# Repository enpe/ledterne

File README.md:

# LEDterne

## Required Equipment

- Suggested hardware lists:
	1. [mikrocontroller.net][0]
- Atmel AVRISP MKII ([Amazon][1])
- Evaluation board ([ehajo][2], [Pollin][3], [Amazon][4])
- Adapter cable, 10P-to-6P ([mikocontroller.net][7], [Amazon 1][5], [Amazon 2][6])
- Power supply (~9V)
- Bread board ([Amazon][8])
- ATMEGA8-16PU ([Amazon][9])
- Steckbrücken 
- Multimeter
- Resistors
- LEDs (e.g. RGB)
- Software (compiler, etc.) ([mikrocontroller.net][20])

## TODO

- Experiment with LEDs
	- Adjust series resistors for balanced LED brightness of the different colors
	- Try diffusing light from the LEDs
- Add some interesting animations
- Add a push button for switching between a number of animations, constant colors etc.
	- Can use pin PD3's external interrupt capabilities instead of polling one of the other free pins
- Make it battery-driven
- Maybe make the PWM smarter for improved energy saving
	- Alternative 1:
		- Avoid generating interrupts for every single possible step in a PWM cycle
		- Compute only the required timeout periods for all 3×5 outputs instead
	- Alternative 2 (easier than 1):
		- Avoid generating interrupts for every single possible step in a PWM cycle
		- Compute only the required timeout periods for all (currently 32) different duty cycles that we actually use
		- This is not as efficient as alternative 1, but it is much simpler to implement since it is not data-dependent (does not change with the desired LED brightness (i.e. with the animations))
- Maybe improve PWM resolution for smoother fading
- Maybe implement the animations using coroutines/generators instead of letting the animation do the diplay update
	- https://en.wikipedia.org/wiki/Generator_%28computer_science%29
	- http://www.chiark.greenend.org.uk/~sgtatham/coroutines.html

### Battery holder and rod
- Dimensions of [mignon/AA batteries][21]:
	- Diameter:  13.5-14.5 mm
    - Length:    49.2-50.5 mm
- General idea:
    1. Rod of the lantern
    	- Thin aluminum tube (outer diameter <= 10mm).
    	- Drill a small hole near the top end of the rod (wire outlet + hook for
    	  lantern).
    	- Close the top end with a small cap (or leave it open).
    	- Take 2-3 corks and drill holes into the centers to fit the rod.
    	- Cut outside part of the corks to fit (tightly) into the tube of 
    	  battery holder.
    	- Slide the corks over the lower end of the rod.
    	- Insert 2 wires from lower end of the rod to the outlet at the top end.
    2. Battery holder
		- Tube with inner diameter of ~15-16 mm.
		- In the first third of the tube, drill a hole for a small switch.
		- Add 2 wires: one from switch to the lower end of the tube the other
		  from one end of the tube to the other.
		- Connect the switch with one wire of the rod, and connect the remaining
		  two wires
		- Connect upper end of the battery holder with the rod.
		- Fill with 3xAA batteries.
		- Add a spring at the lower end and connect it to the wire.
		- Close lower end with a plastic cap (Lamellenstopfen)
- Other DIY project for battery holders (in no particular order):
	- http://makezine.com/2009/08/14/how-to-free-diy-battery-holders/
	- http://makezine.com/2015/08/02/make-a-stylish-flashlight-out-of-kitchen-trash/
	- http://www.instructables.com/id/Bicycle-Battery-Holder-3-x-AA/
	- http://www.instructables.com/id/Easy-custom-battery-holders/
	- http://www.instructables.com/id/Easy-DIY-Battery-Holder/
	- http://www.instructables.com/id/PVC-tube-battery-AA-battery-holder/
	- http://www.pcbheaven.com/projectpages/DIY_Battery_Pack/

[0]: http://www.mikrocontroller.net/articles/AVR-Tutorial:_Equipment
[1]: http://www.amazon.de/Atmel-Programmer-ATMEL-AVR-ISP-MKII/dp/B00CASCN2S
[2]: http://www.ehajo.de/ateval-atmel-evaluationboard.html 
[3]: http://www.pollin.de/shop/dt/NTI5OTgxOTk-/Bausaetze_Module/Entwicklerboards/ATMEL_Evaluations_Board_V2_0_1_Fertigmodul.html
[4]: http://www.amazon.de/Atmel-Fertiggerät-Atmel-Evaluations-Board-V2-0/dp/B004BMJZ0O
[5]: http://www.amazon.de/Convert-Standard-Adapter-STK500-AVRISP/dp/B00P783JIU
[6]: http://www.amazon.de/Adapter-Kit-10polig-Atmel-Programmer/dp/B004D2TFYI
[7]: http://www.mikrocontroller.net/articles/AVR_In_System_Programmer#ISP
[8]: http://www.amazon.de/Steckbrett-Breadboard-Experimentierboard-Steckplatine-Kontakte/dp/B009P04XWW
[9]: http://www.amazon.de/ATMEGA8-16PU-Atmel-Microcontroller-MEGA-DIP-28/dp/9827046934
[20]: http://www.mikrocontroller.net/articles/AVR_und_Linux
[21]: https://de.wikipedia.org/wiki/Mignon_%28Batterie%29

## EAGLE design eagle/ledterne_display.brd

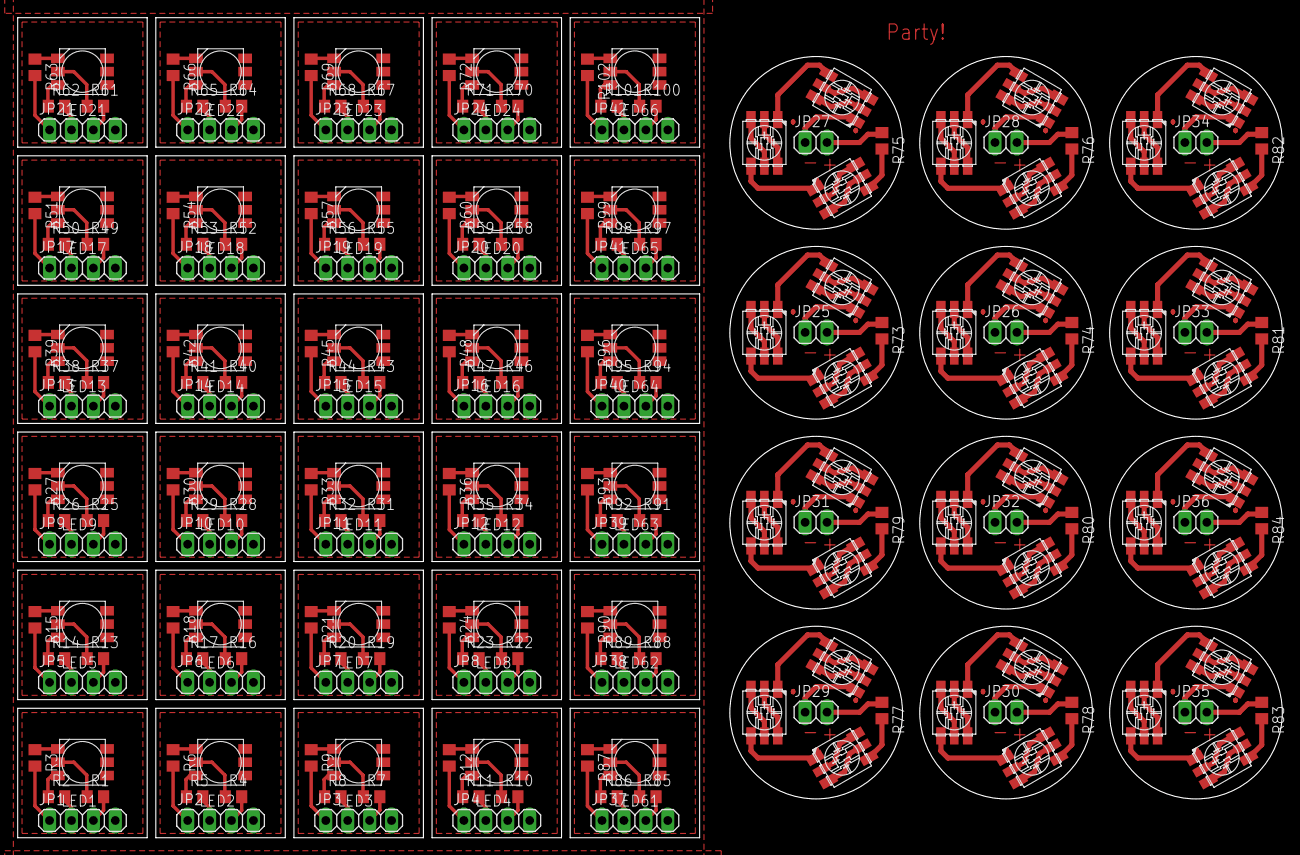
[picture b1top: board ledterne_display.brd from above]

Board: 2 copper layers, 146.5 x 95.0 mm, 210 parts (0 on the bottom side), 342 nets.

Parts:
JP1, JP2, JP3, JP4, JP5, JP6, JP7, JP8, JP9, JP10, JP11, JP12, JP13, JP14, JP15, JP16, JP17, JP18, JP19, JP20, JP21, JP22, JP23, JP24, JP37, JP38, JP39, JP40, JP41, JP42: 1X04
JP25, JP26, JP27, JP28, JP29, JP30, JP31, JP32, JP33, JP34, JP35, JP36: 1X02
LED1, LED2, LED3, LED4, LED5, LED6, LED7, LED8, LED9, LED10, LED11, LED12, LED13, LED14, LED15, LED16, LED17, LED18, LED19, LED20, LED21, LED22, LED23, LED24, LED61, LED62, LED63, LED64, LED65, LED66: RGB-5252; SMD_5252
LED25, LED26, LED27, LED28, LED29, LED30, LED31, LED32, LED33, LED34, LED35, LED36, LED37, LED38, LED39, LED40, LED41, LED42, LED43, LED44, LED45, LED46, LED47, LED48, LED49, LED50, LED51, LED52, LED53, LED54, LED55, LED56, LED57, LED58, LED59, LED60: LUCKYLIGHT-R5050; PLCC-6
R1, R2, R3, R4, R5, R6, R7, R8, R9, R10, R11, R12, R13, R14, R15, R16, R17, R18, R19, R20, R21, R22, R23, R24, R25, R26, R27, R28, R29, R30, R31, R32, R33, R34, R35, R36, R37, R38, R39, R40, R41, R42, R43, R44, R45, R46, R47, R48, R49, R50, R51, R52, R53, R54, R55, R56, R57, R58, R59, R60, R61, R62, R63, R64, R65, R66, R67, R68, R69, R70, R71, R72, R85, R86, R87, R88, R89, R90, R91, R92, R93, R94, R95, R96, R97, R98, R99, R100, R101, R102: R0805
R73, R74, R75, R76, R77, R78, R79, R80, R81, R82, R83, R84: 225; R0805

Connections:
22,5V: JP25.2, R73.1
22,5V1: JP26.2, R74.1
22,5V2: JP27.2, R75.1
22,5V3: JP28.2, R76.1
22,5V4: JP29.2, R77.1
22,5V5: JP30.2, R78.1
22,5V6: JP31.2, R79.1
22,5V7: JP32.2, R80.1
22,5V8: JP33.2, R81.1
22,5V9: JP34.2, R82.1
22,5V10: JP35.2, R83.1
22,5V11: JP36.2, R84.1
GND: JP1.4, LED1.P4, LED1.P5, LED1.P6
GND1: JP2.4, LED2.P4, LED2.P5, LED2.P6
GND2: JP3.4, LED3.P4, LED3.P5, LED3.P6
GND3: JP4.4, LED4.P4, LED4.P5, LED4.P6
GND4: JP5.4, LED5.P4, LED5.P5, LED5.P6
GND5: JP6.4, LED6.P4, LED6.P5, LED6.P6
GND6: JP7.4, LED7.P4, LED7.P5, LED7.P6
GND7: JP8.4, LED8.P4, LED8.P5, LED8.P6
GND8: JP9.4, LED9.P4, LED9.P5, LED9.P6
GND9: JP10.4, LED10.P4, LED10.P5, LED10.P6
GND10: JP11.4, LED11.P4, LED11.P5, LED11.P6
GND11: JP12.4, LED12.P4, LED12.P5, LED12.P6
GND12: JP13.4, LED13.P4, LED13.P5, LED13.P6
GND13: JP14.4, LED14.P4, LED14.P5, LED14.P6
GND14: JP15.4, LED15.P4, LED15.P5, LED15.P6
GND15: JP16.4, LED16.P4, LED16.P5, LED16.P6
GND16: JP17.4, LED17.P4, LED17.P5, LED17.P6
GND17: JP18.4, LED18.P4, LED18.P5, LED18.P6
GND18: JP19.4, LED19.P4, LED19.P5, LED19.P6
GND19: JP20.4, LED20.P4, LED20.P5, LED20.P6
GND20: JP21.4, LED21.P4, LED21.P5, LED21.P6
GND21: JP22.4, LED22.P4, LED22.P5, LED22.P6
GND22: JP23.4, LED23.P4, LED23.P5, LED23.P6
GND23: JP24.4, LED24.P4, LED24.P5, LED24.P6
GND24: JP25.1, LED27.P$1
GND25: JP26.1, LED30.P$1
GND26: JP27.1, LED33.P$1
GND27: JP28.1, LED36.P$1
GND28: JP29.1, LED39.P$1
GND29: JP30.1, LED42.P$1
GND30: JP31.1, LED45.P$1
GND31: JP32.1, LED48.P$1
GND32: JP33.1, LED51.P$1
GND33: JP34.1, LED54.P$1
GND34: JP35.1, LED57.P$1
GND35: JP36.1, LED60.P$1
GND36: JP37.4, LED61.P4, LED61.P5, LED61.P6
GND37: JP38.4, LED62.P4, LED62.P5, LED62.P6
GND38: JP39.4, LED63.P4, LED63.P5, LED63.P6
GND39: JP40.4, LED64.P4, LED64.P5, LED64.P6
GND40: JP41.4, LED65.P4, LED65.P5, LED65.P6
GND41: JP42.4, LED66.P4, LED66.P5, LED66.P6
LED_B: JP1.1, R3.2
LED_B1: JP2.1, R6.2
LED_B2: JP3.1, R9.2
LED_B3: JP4.1, R12.2
LED_B4: JP5.1, R15.2
LED_B5: JP6.1, R18.2
LED_B6: JP7.1, R21.2
LED_B7: JP8.1, R24.2
LED_B8: JP9.1, R27.2
LED_B9: JP10.1, R30.2
LED_B10: JP11.1, R33.2
LED_B11: JP12.1, R36.2
LED_B12: JP13.1, R39.2
LED_B13: JP14.1, R42.2
LED_B14: JP15.1, R45.2
LED_B15: JP16.1, R48.2
LED_B16: JP17.1, R51.2
LED_B17: JP18.1, R54.2
LED_B18: JP19.1, R57.2
LED_B19: JP20.1, R60.2
LED_B20: JP21.1, R63.2
LED_B21: JP22.1, R66.2
LED_B22: JP23.1, R69.2
LED_B23: JP24.1, R72.2
LED_B24: JP37.1, R87.2
LED_B25: JP38.1, R90.2
LED_B26: JP39.1, R93.2
LED_B27: JP40.1, R96.2
LED_B28: JP41.1, R99.2
LED_B29: JP42.1, R102.2
LED_G: JP1.2, R2.2
LED_G1: JP2.2, R5.2
LED_G2: JP3.2, R8.2
LED_G3: JP4.2, R11.2
LED_G4: JP5.2, R14.2
LED_G5: JP6.2, R17.2
LED_G6: JP7.2, R20.2
LED_G7: JP8.2, R23.2
LED_G8: JP9.2, R26.2
LED_G9: JP10.2, R29.2
LED_G10: JP11.2, R32.2
LED_G11: JP12.2, R35.2
LED_G12: JP13.2, R38.2
LED_G13: JP14.2, R41.2
LED_G14: JP15.2, R44.2
LED_G15: JP16.2, R47.2
LED_G16: JP17.2, R50.2
LED_G17: JP18.2, R53.2
LED_G18: JP19.2, R56.2
LED_G19: JP20.2, R59.2
LED_G20: JP21.2, R62.2
LED_G21: JP22.2, R65.2
LED_G22: JP23.2, R68.2
LED_G23: JP24.2, R71.2
LED_G24: JP37.2, R86.2
LED_G25: JP38.2, R89.2
LED_G26: JP39.2, R92.2
LED_G27: JP40.2, R95.2
LED_G28: JP41.2, R98.2
LED_G29: JP42.2, R101.2
LED_R: JP1.3, R1.2
LED_R1: JP2.3, R4.2
LED_R2: JP3.3, R7.2
LED_R3: JP4.3, R10.2
LED_R4: JP5.3, R13.2
LED_R5: JP6.3, R16.2
LED_R6: JP7.3, R19.2
LED_R7: JP8.3, R22.2
LED_R8: JP9.3, R25.2
LED_R9: JP10.3, R28.2
LED_R10: JP11.3, R31.2
LED_R11: JP12.3, R34.2
LED_R12: JP13.3, R37.2
LED_R13: JP14.3, R40.2
LED_R14: JP15.3, R43.2
LED_R15: JP16.3, R46.2
LED_R16: JP17.3, R49.2
LED_R17: JP18.3, R52.2
LED_R18: JP19.3, R55.2
LED_R19: JP20.3, R58.2
LED_R20: JP21.3, R61.2
LED_R21: JP22.3, R64.2
LED_R22: JP23.3, R67.2
LED_R23: JP24.3, R70.2
LED_R24: JP37.3, R85.2
LED_R25: JP38.3, R88.2
LED_R26: JP39.3, R91.2
LED_R27: JP40.3, R94.2
LED_R28: JP41.3, R97.2
LED_R29: JP42.3, R100.2
unnamed: LED1.P2, R1.1
unnamed: LED1.P3, R2.1
unnamed: LED1.P1, R3.1
unnamed: LED2.P2, R4.1
unnamed: LED2.P3, R5.1
unnamed: LED2.P1, R6.1
unnamed: LED3.P2, R7.1
unnamed: LED3.P3, R8.1
unnamed: LED3.P1, R9.1
unnamed: LED4.P2, R10.1
unnamed: LED4.P3, R11.1
unnamed: LED4.P1, R12.1
unnamed: LED5.P2, R13.1
unnamed: LED5.P3, R14.1
unnamed: LED5.P1, R15.1
unnamed: LED6.P2, R16.1
unnamed: LED6.P3, R17.1
unnamed: LED6.P1, R18.1
unnamed: LED7.P2, R19.1
unnamed: LED7.P3, R20.1
unnamed: LED7.P1, R21.1
unnamed: LED8.P2, R22.1
unnamed: LED8.P3, R23.1
unnamed: LED8.P1, R24.1
unnamed: LED9.P2, R25.1
unnamed: LED9.P3, R26.1
unnamed: LED9.P1, R27.1
unnamed: LED10.P2, R28.1
unnamed: LED10.P3, R29.1
unnamed: LED10.P1, R30.1
unnamed: LED11.P2, R31.1
unnamed: LED11.P3, R32.1
unnamed: LED11.P1, R33.1
unnamed: LED12.P2, R34.1
unnamed: LED12.P3, R35.1
unnamed: LED12.P1, R36.1
unnamed: LED13.P2, R37.1
unnamed: LED13.P3, R38.1
unnamed: LED13.P1, R39.1
unnamed: LED14.P2, R40.1
unnamed: LED14.P3, R41.1
unnamed: LED14.P1, R42.1
unnamed: LED15.P2, R43.1
unnamed: LED15.P3, R44.1
unnamed: LED15.P1, R45.1
unnamed: LED16.P2, R46.1
unnamed: LED16.P3, R47.1
unnamed: LED16.P1, R48.1
unnamed: LED17.P2, R49.1
unnamed: LED17.P3, R50.1
unnamed: LED17.P1, R51.1
unnamed: LED18.P2, R52.1
unnamed: LED18.P3, R53.1
unnamed: LED18.P1, R54.1
unnamed: LED19.P2, R55.1
unnamed: LED19.P3, R56.1
unnamed: LED19.P1, R57.1
unnamed: LED20.P2, R58.1
unnamed: LED20.P3, R59.1
unnamed: LED20.P1, R60.1
unnamed: LED21.P2, R61.1
unnamed: LED21.P3, R62.1
unnamed: LED21.P1, R63.1
unnamed: LED22.P2, R64.1
unnamed: LED22.P3, R65.1
unnamed: LED22.P1, R66.1
unnamed: LED23.P2, R67.1
unnamed: LED23.P3, R68.1
unnamed: LED23.P1, R69.1
unnamed: LED24.P2, R70.1
unnamed: LED24.P3, R71.1
unnamed: LED24.P1, R72.1
unnamed: LED27.P$2, LED27.P$6
unnamed: LED27.P$3, LED27.P$5
unnamed: LED26.P$1, LED27.P$4
unnamed: LED26.P$2, LED26.P$6
unnamed: LED26.P$3, LED26.P$5
unnamed: LED25.P$1, LED26.P$4
unnamed: LED25.P$2, LED25.P$6
unnamed: LED25.P$3, LED25.P$5
unnamed: LED25.P$4, R73.2
unnamed: LED30.P$2, LED30.P$6
unnamed: LED30.P$3, LED30.P$5
unnamed: LED29.P$1, LED30.P$4
unnamed: LED29.P$2, LED29.P$6
unnamed: LED29.P$3, LED29.P$5
unnamed: LED28.P$1, LED29.P$4
unnamed: LED28.P$2, LED28.P$6
unnamed: LED28.P$3, LED28.P$5
unnamed: LED28.P$4, R74.2
unnamed: LED33.P$2, LED33.P$6
unnamed: LED33.P$3, LED33.P$5
unnamed: LED32.P$1, LED33.P$4
unnamed: LED32.P$2, LED32.P$6
unnamed: LED32.P$3, LED32.P$5
unnamed: LED31.P$1, LED32.P$4
unnamed: LED31.P$2, LED31.P$6
unnamed: LED31.P$3, LED31.P$5
unnamed: LED31.P$4, R75.2
unnamed: LED36.P$2, LED36.P$6
unnamed: LED36.P$3, LED36.P$5
unnamed: LED35.P$1, LED36.P$4
unnamed: LED35.P$2, LED35.P$6
unnamed: LED35.P$3, LED35.P$5
unnamed: LED34.P$1, LED35.P$4
unnamed: LED34.P$2, LED34.P$6
unnamed: LED34.P$3, LED34.P$5
unnamed: LED34.P$4, R76.2
unnamed: LED39.P$2, LED39.P$6
unnamed: LED39.P$3, LED39.P$5
unnamed: LED38.P$1, LED39.P$4
unnamed: LED38.P$2, LED38.P$6
unnamed: LED38.P$3, LED38.P$5
unnamed: LED37.P$1, LED38.P$4
unnamed: LED37.P$2, LED37.P$6
unnamed: LED37.P$3, LED37.P$5
unnamed: LED37.P$4, R77.2
unnamed: LED42.P$2, LED42.P$6
unnamed: LED42.P$3, LED42.P$5
unnamed: LED41.P$1, LED42.P$4
unnamed: LED41.P$2, LED41.P$6
unnamed: LED41.P$3, LED41.P$5
unnamed: LED40.P$1, LED41.P$4
unnamed: LED40.P$2, LED40.P$6
unnamed: LED40.P$3, LED40.P$5
unnamed: LED40.P$4, R78.2
unnamed: LED45.P$2, LED45.P$6
unnamed: LED45.P$3, LED45.P$5
unnamed: LED44.P$1, LED45.P$4
unnamed: LED44.P$2, LED44.P$6
unnamed: LED44.P$3, LED44.P$5
unnamed: LED43.P$1, LED44.P$4
unnamed: LED43.P$2, LED43.P$6
unnamed: LED43.P$3, LED43.P$5
unnamed: LED43.P$4, R79.2
unnamed: LED48.P$2, LED48.P$6
unnamed: LED48.P$3, LED48.P$5
unnamed: LED47.P$1, LED48.P$4
unnamed: LED47.P$2, LED47.P$6
unnamed: LED47.P$3, LED47.P$5
unnamed: LED46.P$1, LED47.P$4
unnamed: LED46.P$2, LED46.P$6
unnamed: LED46.P$3, LED46.P$5
unnamed: LED46.P$4, R80.2
unnamed: LED51.P$2, LED51.P$6
unnamed: LED51.P$3, LED51.P$5
unnamed: LED50.P$1, LED51.P$4
unnamed: LED50.P$2, LED50.P$6
unnamed: LED50.P$3, LED50.P$5
unnamed: LED49.P$1, LED50.P$4
unnamed: LED49.P$2, LED49.P$6
unnamed: LED49.P$3, LED49.P$5
unnamed: LED49.P$4, R81.2
unnamed: LED54.P$2, LED54.P$6
unnamed: LED54.P$3, LED54.P$5
unnamed: LED53.P$1, LED54.P$4
unnamed: LED53.P$2, LED53.P$6
unnamed: LED53.P$3, LED53.P$5
unnamed: LED52.P$1, LED53.P$4
unnamed: LED52.P$2, LED52.P$6
unnamed: LED52.P$3, LED52.P$5
unnamed: LED52.P$4, R82.2
unnamed: LED57.P$2, LED57.P$6
unnamed: LED57.P$3, LED57.P$5
unnamed: LED56.P$1, LED57.P$4
unnamed: LED56.P$2, LED56.P$6
unnamed: LED56.P$3, LED56.P$5
unnamed: LED55.P$1, LED56.P$4
unnamed: LED55.P$2, LED55.P$6
unnamed: LED55.P$3, LED55.P$5
unnamed: LED55.P$4, R83.2
unnamed: LED60.P$2, LED60.P$6
unnamed: LED60.P$3, LED60.P$5
unnamed: LED59.P$1, LED60.P$4
unnamed: LED59.P$2, LED59.P$6
unnamed: LED59.P$3, LED59.P$5
unnamed: LED58.P$1, LED59.P$4
unnamed: LED58.P$2, LED58.P$6
unnamed: LED58.P$3, LED58.P$5
unnamed: LED58.P$4, R84.2
unnamed: LED61.P2, R85.1
unnamed: LED61.P3, R86.1
unnamed: LED61.P1, R87.1
unnamed: LED62.P2, R88.1
unnamed: LED62.P3, R89.1
unnamed: LED62.P1, R90.1
unnamed: LED63.P2, R91.1
unnamed: LED63.P3, R92.1
unnamed: LED63.P1, R93.1
unnamed: LED64.P2, R94.1
unnamed: LED64.P3, R95.1
unnamed: LED64.P1, R96.1
unnamed: LED65.P2, R97.1
unnamed: LED65.P3, R98.1
unnamed: LED65.P1, R99.1
unnamed: LED66.P2, R100.1
unnamed: LED66.P3, R101.1
unnamed: LED66.P1, R102.1

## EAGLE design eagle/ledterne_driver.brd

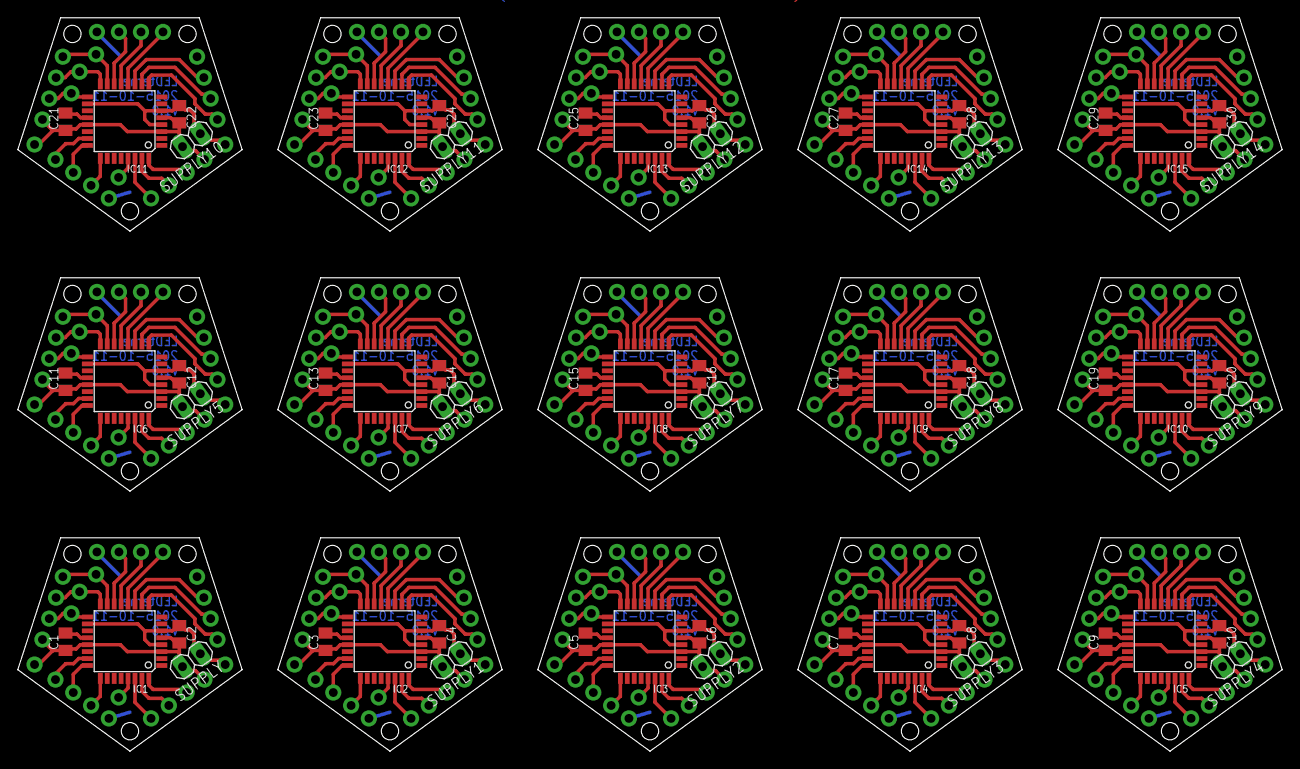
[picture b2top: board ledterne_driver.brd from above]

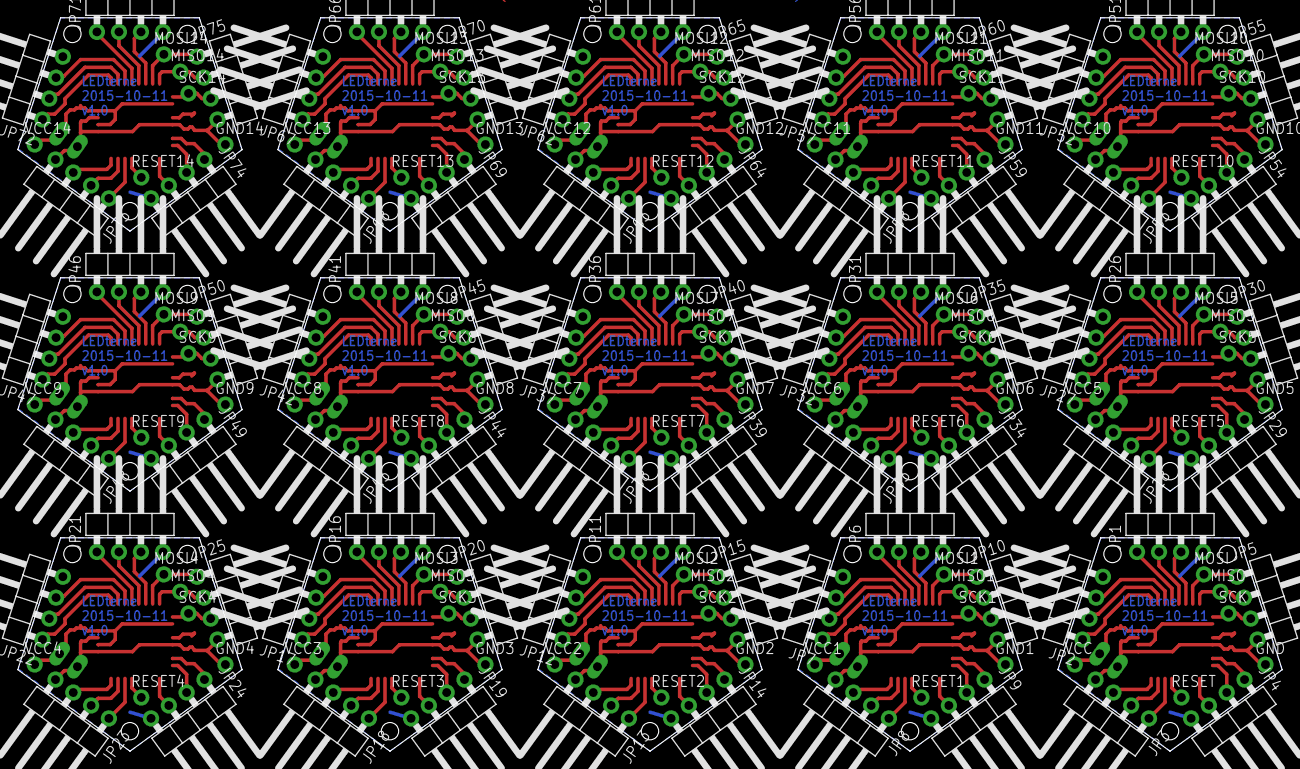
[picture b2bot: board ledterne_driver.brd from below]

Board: 2 copper layers, 145.9 x 84.6 mm, 225 parts (165 on the bottom side), 285 nets.

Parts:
C1, C2, C3, C4, C5, C6, C7, C8, C9, C10, C11, C12, C13, C14, C15, C16, C17, C18, C19, C20, C21, C22, C23, C24, C25, C26, C27, C28, C29, C30: 100n; C0805K
GND, GND1, GND2, GND3, GND4, GND5, GND6, GND7, GND8, GND9, GND10, GND11, GND12, GND13, GND14: LSP10
IC1, IC2, IC3, IC4, IC5, IC6, IC7, IC8, IC9, IC10, IC11, IC12, IC13, IC14, IC15: MEGA8-AI; TQFP32-08
JP1, JP2, JP3, JP4, JP5, JP6, JP7, JP8, JP9, JP10, JP11, JP12, JP13, JP14, JP15, JP16, JP17, JP18, JP19, JP20, JP21, JP22, JP23, JP24, JP25, JP26, JP27, JP28, JP29, JP30, JP31, JP32, JP33, JP34, JP35, JP36, JP37, JP38, JP39, JP40, JP41, JP42, JP43, JP44, JP45, JP46, JP47, JP48, JP49, JP50, JP51, JP52, JP53, JP54, JP55, JP56, JP57, JP58, JP59, JP60, JP61, JP62, JP63, JP64, JP65, JP66, JP67, JP68, JP69, JP70, JP71, JP72, JP73, JP74, JP75: 1X04/90
MISO, MISO1, MISO2, MISO3, MISO4, MISO5, MISO6, MISO7, MISO8, MISO9, MISO10, MISO11, MISO12, MISO13, MISO14: LSP10
MOSI, MOSI1, MOSI2, MOSI3, MOSI4, MOSI5, MOSI6, MOSI7, MOSI8, MOSI9, MOSI10, MOSI11, MOSI12, MOSI13, MOSI14: LSP10
RESET, RESET1, RESET2, RESET3, RESET4, RESET5, RESET6, RESET7, RESET8, RESET9, RESET10, RESET11, RESET12, RESET13, RESET14: LSP10
SCK, SCK1, SCK2, SCK3, SCK4, SCK5, SCK6, SCK7, SCK8, SCK9, SCK10, SCK11, SCK12, SCK13, SCK14: LSP10
SUPPLY, SUPPLY1, SUPPLY2, SUPPLY3, SUPPLY4, SUPPLY5, SUPPLY6, SUPPLY7, SUPPLY8, SUPPLY9, SUPPLY10, SUPPLY11, SUPPLY12, SUPPLY13, SUPPLY14: 1X02
VCC, VCC1, VCC2, VCC3, VCC4, VCC5, VCC6, VCC7, VCC8, VCC9, VCC10, VCC11, VCC12, VCC13, VCC14: LSP10

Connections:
GND: C1.1, C2.2, GND.MP, IC1.3, IC1.5, IC1.21, JP1.4, JP2.4, JP3.4, JP4.4, JP5.4, SUPPLY.2
GND1: C3.1, C4.2, GND1.MP, IC2.3, IC2.5, IC2.21, JP6.4, JP7.4, JP8.4, JP9.4, JP10.4, SUPPLY1.2
GND2: C5.1, C6.2, GND2.MP, IC3.3, IC3.5, IC3.21, JP11.4, JP12.4, JP13.4, JP14.4, JP15.4, SUPPLY2.2
GND3: C7.1, C8.2, GND3.MP, IC4.3, IC4.5, IC4.21, JP16.4, JP17.4, JP18.4, JP19.4, JP20.4, SUPPLY3.2
GND4: C9.1, C10.2, GND4.MP, IC5.3, IC5.5, IC5.21, JP21.4, JP22.4, JP23.4, JP24.4, JP25.4, SUPPLY4.2
GND5: C11.1, C12.2, GND5.MP, IC6.3, IC6.5, IC6.21, JP26.4, JP27.4, JP28.4, JP29.4, JP30.4, SUPPLY5.2
GND6: C13.1, C14.2, GND6.MP, IC7.3, IC7.5, IC7.21, JP31.4, JP32.4, JP33.4, JP34.4, JP35.4, SUPPLY6.2
GND7: C15.1, C16.2, GND7.MP, IC8.3, IC8.5, IC8.21, JP36.4, JP37.4, JP38.4, JP39.4, JP40.4, SUPPLY7.2
GND8: C17.1, C18.2, GND8.MP, IC9.3, IC9.5, IC9.21, JP41.4, JP42.4, JP43.4, JP44.4, JP45.4, SUPPLY8.2
GND9: C19.1, C20.2, GND9.MP, IC10.3, IC10.5, IC10.21, JP46.4, JP47.4, JP48.4, JP49.4, JP50.4, SUPPLY9.2
GND10: C21.1, C22.2, GND10.MP, IC11.3, IC11.5, IC11.21, JP51.4, JP52.4, JP53.4, JP54.4, JP55.4, SUPPLY10.2
GND11: C23.1, C24.2, GND11.MP, IC12.3, IC12.5, IC12.21, JP56.4, JP57.4, JP58.4, JP59.4, JP60.4, SUPPLY11.2
GND12: C25.1, C26.2, GND12.MP, IC13.3, IC13.5, IC13.21, JP61.4, JP62.4, JP63.4, JP64.4, JP65.4, SUPPLY12.2
GND13: C27.1, C28.2, GND13.MP, IC14.3, IC14.5, IC14.21, JP66.4, JP67.4, JP68.4, JP69.4, JP70.4, SUPPLY13.2
GND14: C29.1, C30.2, GND14.MP, IC15.3, IC15.5, IC15.21, JP71.4, JP72.4, JP73.4, JP74.4, JP75.4, SUPPLY14.2
MISO: IC1.16, JP5.2, MISO.MP
MISO1: IC2.16, JP10.2, MISO1.MP
MISO2: IC3.16, JP15.2, MISO2.MP
MISO3: IC4.16, JP20.2, MISO3.MP
MISO4: IC5.16, JP25.2, MISO4.MP
MISO5: IC6.16, JP30.2, MISO5.MP
MISO6: IC7.16, JP35.2, MISO6.MP
MISO7: IC8.16, JP40.2, MISO7.MP
MISO8: IC9.16, JP45.2, MISO8.MP
MISO9: IC10.16, JP50.2, MISO9.MP
MISO10: IC11.16, JP55.2, MISO10.MP
MISO11: IC12.16, JP60.2, MISO11.MP
MISO12: IC13.16, JP65.2, MISO12.MP
MISO13: IC14.16, JP70.2, MISO13.MP
MISO14: IC15.16, JP75.2, MISO14.MP
MOSI: IC1.15, JP5.1, MOSI.MP
MOSI1: IC2.15, JP10.1, MOSI1.MP
MOSI2: IC3.15, JP15.1, MOSI2.MP
MOSI3: IC4.15, JP20.1, MOSI3.MP
MOSI4: IC5.15, JP25.1, MOSI4.MP
MOSI5: IC6.15, JP30.1, MOSI5.MP
MOSI6: IC7.15, JP35.1, MOSI6.MP
MOSI7: IC8.15, JP40.1, MOSI7.MP
MOSI8: IC9.15, JP45.1, MOSI8.MP
MOSI9: IC10.15, JP50.1, MOSI9.MP
MOSI10: IC11.15, JP55.1, MOSI10.MP
MOSI11: IC12.15, JP60.1, MOSI11.MP
MOSI12: IC13.15, JP65.1, MOSI12.MP
MOSI13: IC14.15, JP70.1, MOSI13.MP
MOSI14: IC15.15, JP75.1, MOSI14.MP
unnamed: C1.2, IC1.20
unnamed: C3.2, IC2.20
unnamed: IC1.14, JP1.3
unnamed: IC1.13, JP1.2
unnamed: IC1.12, JP1.1
unnamed: IC1.11, JP2.3
unnamed: IC1.10, JP2.2
unnamed: IC1.9, JP2.1
unnamed: IC1.30, JP3.1
unnamed: IC1.31, JP3.2
unnamed: IC1.32, JP3.3
unnamed: IC1.23, JP4.1
unnamed: IC1.24, JP4.2
unnamed: IC2.14, JP6.3
unnamed: IC1.25, JP4.3
unnamed: IC2.13, JP6.2
unnamed: IC2.12, JP6.1
unnamed: IC2.11, JP7.3
unnamed: IC2.10, JP7.2
unnamed: IC2.9, JP7.1
unnamed: IC2.30, JP8.1
unnamed: IC2.31, JP8.2
unnamed: IC2.32, JP8.3
unnamed: IC2.23, JP9.1
unnamed: IC2.24, JP9.2
unnamed: IC2.25, JP9.3
unnamed: C5.2, IC3.20
unnamed: IC3.14, JP11.3
unnamed: IC3.13, JP11.2
unnamed: IC3.12, JP11.1
unnamed: IC3.11, JP12.3
unnamed: IC3.10, JP12.2
unnamed: IC3.9, JP12.1
unnamed: IC3.30, JP13.1
unnamed: IC3.31, JP13.2
unnamed: IC3.32, JP13.3
unnamed: IC3.23, JP14.1
unnamed: IC3.24, JP14.2
unnamed: IC3.25, JP14.3
unnamed: C7.2, IC4.20
unnamed: IC4.14, JP16.3
unnamed: IC4.13, JP16.2
unnamed: IC4.12, JP16.1
unnamed: IC4.11, JP17.3
unnamed: IC4.10, JP17.2
unnamed: IC4.9, JP17.1
unnamed: IC4.30, JP18.1
unnamed: IC4.31, JP18.2
unnamed: IC4.32, JP18.3
unnamed: IC4.23, JP19.1
unnamed: IC4.24, JP19.2
unnamed: IC4.25, JP19.3
unnamed: C9.2, IC5.20
unnamed: IC5.14, JP21.3
unnamed: IC5.13, JP21.2
unnamed: IC5.12, JP21.1
unnamed: IC5.11, JP22.3
unnamed: IC5.10, JP22.2
unnamed: IC5.9, JP22.1
unnamed: IC5.30, JP23.1
unnamed: IC5.31, JP23.2
unnamed: IC5.32, JP23.3
unnamed: IC5.23, JP24.1
unnamed: IC5.24, JP24.2
unnamed: IC5.25, JP24.3
unnamed: C11.2, IC6.20
unnamed: IC6.14, JP26.3
unnamed: IC6.13, JP26.2
unnamed: IC6.12, JP26.1
unnamed: IC6.11, JP27.3
unnamed: IC6.10, JP27.2
unnamed: IC6.9, JP27.1
unnamed: IC6.30, JP28.1
unnamed: IC6.31, JP28.2
unnamed: IC6.32, JP28.3
unnamed: IC6.23, JP29.1
unnamed: IC6.24, JP29.2
unnamed: IC6.25, JP29.3
unnamed: C13.2, IC7.20
unnamed: IC7.14, JP31.3
unnamed: IC7.13, JP31.2
unnamed: IC7.12, JP31.1
unnamed: IC7.11, JP32.3
unnamed: IC7.10, JP32.2
unnamed: IC7.9, JP32.1
unnamed: IC7.30, JP33.1
unnamed: IC7.31, JP33.2
unnamed: IC7.32, JP33.3
unnamed: IC7.23, JP34.1
unnamed: IC7.24, JP34.2
unnamed: IC7.25, JP34.3
unnamed: C15.2, IC8.20
unnamed: IC8.14, JP36.3
unnamed: IC8.13, JP36.2
unnamed: IC8.12, JP36.1
unnamed: IC8.11, JP37.3
unnamed: IC8.10, JP37.2
unnamed: IC8.9, JP37.1
unnamed: IC8.30, JP38.1
unnamed: IC8.31, JP38.2
unnamed: IC8.32, JP38.3
unnamed: IC8.23, JP39.1
unnamed: IC8.24, JP39.2
unnamed: IC8.25, JP39.3
unnamed: C17.2, IC9.20
unnamed: IC9.14, JP41.3
unnamed: IC9.13, JP41.2
unnamed: IC9.12, JP41.1
unnamed: IC9.11, JP42.3
unnamed: IC9.10, JP42.2
unnamed: IC9.9, JP42.1
unnamed: IC9.30, JP43.1
unnamed: IC9.31, JP43.2
unnamed: IC9.32, JP43.3
unnamed: IC9.23, JP44.1
unnamed: IC9.24, JP44.2
unnamed: IC9.25, JP44.3
unnamed: C19.2, IC10.20
unnamed: IC10.14, JP46.3
unnamed: IC10.13, JP46.2
unnamed: IC10.12, JP46.1
unnamed: IC10.11, JP47.3
unnamed: IC10.10, JP47.2
unnamed: IC10.9, JP47.1
unnamed: IC10.30, JP48.1
unnamed: IC10.31, JP48.2
unnamed: IC10.32, JP48.3
unnamed: IC10.23, JP49.1
unnamed: IC10.24, JP49.2
unnamed: IC10.25, JP49.3
unnamed: C21.2, IC11.20
unnamed: IC11.14, JP51.3
unnamed: IC11.13, JP51.2
unnamed: IC11.12, JP51.1
unnamed: IC11.11, JP52.3
unnamed: IC11.10, JP52.2
unnamed: IC11.9, JP52.1
unnamed: IC11.30, JP53.1
unnamed: IC11.31, JP53.2
unnamed: IC11.32, JP53.3
unnamed: IC11.23, JP54.1
unnamed: IC11.24, JP54.2
unnamed: IC11.25, JP54.3
unnamed: C23.2, IC12.20
unnamed: IC12.14, JP56.3
unnamed: IC12.13, JP56.2
unnamed: IC12.12, JP56.1
unnamed: IC12.11, JP57.3
unnamed: IC12.10, JP57.2
unnamed: IC12.9, JP57.1
unnamed: IC12.30, JP58.1
unnamed: IC12.31, JP58.2
unnamed: IC12.32, JP58.3
unnamed: IC12.23, JP59.1
unnamed: IC12.24, JP59.2
unnamed: IC12.25, JP59.3
unnamed: C25.2, IC13.20
unnamed: IC13.14, JP61.3
unnamed: IC13.13, JP61.2
unnamed: IC13.12, JP61.1
unnamed: IC13.11, JP62.3
unnamed: IC13.10, JP62.2
unnamed: IC13.9, JP62.1
unnamed: IC13.30, JP63.1
unnamed: IC13.31, JP63.2
unnamed: IC13.32, JP63.3
unnamed: IC13.23, JP64.1
unnamed: IC13.24, JP64.2
unnamed: IC13.25, JP64.3
unnamed: C27.2, IC14.20
unnamed: IC14.14, JP66.3
unnamed: IC14.13, JP66.2
unnamed: IC14.12, JP66.1
unnamed: IC14.11, JP67.3
unnamed: IC14.10, JP67.2
unnamed: IC14.9, JP67.1
unnamed: IC14.30, JP68.1
unnamed: IC14.31, JP68.2
unnamed: IC14.32, JP68.3
unnamed: IC14.23, JP69.1
unnamed: IC14.24, JP69.2
unnamed: IC14.25, JP69.3
unnamed: C29.2, IC15.20
unnamed: IC15.14, JP71.3
unnamed: IC15.13, JP71.2
unnamed: IC15.12, JP71.1
unnamed: IC15.11, JP72.3
unnamed: IC15.10, JP72.2
unnamed: IC15.9, JP72.1
unnamed: IC15.30, JP73.1
unnamed: IC15.31, JP73.2
unnamed: IC15.32, JP73.3
unnamed: IC15.23, JP74.1
unnamed: IC15.24, JP74.2
unnamed: IC15.25, JP74.3
RESET: IC1.29, RESET.MP
RESET1: IC2.29, RESET1.MP
RESET2: IC3.29, RESET2.MP
RESET3: IC4.29, RESET3.MP
RESET4: IC5.29, RESET4.MP
RESET5: IC6.29, RESET5.MP
RESET6: IC7.29, RESET6.MP
RESET7: IC8.29, RESET7.MP
RESET8: IC9.29, RESET8.MP
RESET9: IC10.29, RESET9.MP
RESET10: IC11.29, RESET10.MP
RESET11: IC12.29, RESET11.MP
RESET12: IC13.29, RESET12.MP
RESET13: IC14.29, RESET13.MP
RESET14: IC15.29, RESET14.MP
SCK: IC1.17, JP5.3, SCK.MP
SCK1: IC2.17, JP10.3, SCK1.MP
SCK2: IC3.17, JP15.3, SCK2.MP
SCK3: IC4.17, JP20.3, SCK3.MP
SCK4: IC5.17, JP25.3, SCK4.MP
SCK5: IC6.17, JP30.3, SCK5.MP
SCK6: IC7.17, JP35.3, SCK6.MP
SCK7: IC8.17, JP40.3, SCK7.MP
SCK8: IC9.17, JP45.3, SCK8.MP
SCK9: IC10.17, JP50.3, SCK9.MP
SCK10: IC11.17, JP55.3, SCK10.MP
SCK11: IC12.17, JP60.3, SCK11.MP
SCK12: IC13.17, JP65.3, SCK12.MP
SCK13: IC14.17, JP70.3, SCK13.MP
SCK14: IC15.17, JP75.3, SCK14.MP
VCC: C2.1, IC1.4, IC1.6, IC1.18, SUPPLY.1, VCC.MP
VCC1: C4.1, IC2.4, IC2.6, IC2.18, SUPPLY1.1, VCC1.MP
VCC2: C6.1, IC3.4, IC3.6, IC3.18, SUPPLY2.1, VCC2.MP
VCC3: C8.1, IC4.4, IC4.6, IC4.18, SUPPLY3.1, VCC3.MP
VCC4: C10.1, IC5.4, IC5.6, IC5.18, SUPPLY4.1, VCC4.MP
VCC5: C12.1, IC6.4, IC6.6, IC6.18, SUPPLY5.1, VCC5.MP
VCC6: C14.1, IC7.4, IC7.6, IC7.18, SUPPLY6.1, VCC6.MP
VCC7: C16.1, IC8.4, IC8.6, IC8.18, SUPPLY7.1, VCC7.MP
VCC8: C18.1, IC9.4, IC9.6, IC9.18, SUPPLY8.1, VCC8.MP
VCC9: C20.1, IC10.4, IC10.6, IC10.18, SUPPLY9.1, VCC9.MP
VCC10: C22.1, IC11.4, IC11.6, IC11.18, SUPPLY10.1, VCC10.MP
VCC11: C24.1, IC12.4, IC12.6, IC12.18, SUPPLY11.1, VCC11.MP
VCC12: C26.1, IC13.4, IC13.6, IC13.18, SUPPLY12.1, VCC12.MP
VCC13: C28.1, IC14.4, IC14.6, IC14.18, SUPPLY13.1, VCC13.MP
VCC14: C30.1, IC15.4, IC15.6, IC15.18, SUPPLY14.1, VCC14.MP
